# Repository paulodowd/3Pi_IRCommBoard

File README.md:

# 3Pi_IRCommBoard (work in progress)

## Features

- Can be considered a general purpose I2C extension board to provide local infra-red (IR) communication.
- IR Serial transmission at 4800 Baud.
- Transmit/receive upto 28 bytes (currently, extensible).
- Range can be reduced/set with a trimmer potentiometer.
- Effective IR transmit range approximately 30cm.
- Message corruption detection implemented with a CRC checksum.
- Designed to conveniently fit to an expansion header of the Pololu 3Pi+ mobile robot. 

## Summary

A pcb design to create infra-red (IR) communication between Pololu 3Pi+ robots. The design utilises an Arduino Pro Mini as an I2C Slave device.  The pro mini handles all transmit and receive operations over IR. The Master device (inteded as the 3Pi+, but could be any device with I2C) can upload a string to transmit, and also request the latest string received, if any.  This can get a little confusing to discuss: I2C is used to transfer messages between Master and Slave, and Serial/IR is used to tranmit messages between Slave devices.  

IR communication is implemented using the standard Serial functionality common to Arduino (e.g. `Serial.print()`), and so the IR circuit is electronically connected to  the Arduino TX and RX pins.  The detection (receiving) circuit uses a Demodulator chip that is tuned for a carrier frequency of 38.4Khz (more details below).  Therefore, the pro mini generates a 38Khz signal via an internal timer interrupt to provide the transmitting carrier, output on digital pin 4.  

The 38Khz carrier signal is combined electronically with the TX pin state through an OR gate (74xx32). The logic (OR) of this operation is defined by the gates sinking the current through the tranmitting IR LEDs.  Therefore, the LEDs are not driven by the 74xx32 (or the pro mini, to be clear), and are considered active low.  A nice unintended side effect of this is that when TX is inactive (LOW, not transmitting), the 74xx32 output is HIGH despite the continued 38Khz signal generation - which means the IR LEDs are off and not saturating the environment.

In this circuit design, a single gate is used to sink current.  It might be important to note that the <a href="https://www.ti.com/lit/ds/symlink/sn54hc32-sp.pdf">datasheet</a> for the logic gates specifies a max current sink of 50ma through ground - and here we are potentially sinking upto 250ma from the 5 IR LEDs.    So far, I've not seen any significant changes to performance and this may be because I am not sinking current continuously, instead intermitently at 38Khz. In a subsequent design (available <a href="https://github.com/paulodowd/Swarm-Bs">here</a>), all 4 gates are ganged, but the internal ground connection may still be a limitation. In either case, I haven't yet seen any problems or difference in performance.  It might be unwise to active the IR LEDs continuously.

Some messages transmitted over IR do get garbled.  As a quick solution, the firmware uses a CRC checksum.  I've used the same implementation as detailed on the RepRap wiki for GCode (<a href="https://reprap.org/wiki/G-code#Checking">here</a>).  Prior to transmitting, the pro mini generates a single byte checksum value, and appends this to the message string.  Therefore, when a message is received, the receiving pro mini completes the same CRC check on the received message for itself, and then compares if the checksum values match.  If not, some data must be corrupt and the message is discarded.  

The message strings transmitted between the pro mini devices would look something like:

`*message string@f`

Here, the `*` is used to identify the start of a message, the `@` is used to identify the end of the message and that the next byte is the checksum value.  In the example above, I haven't used the correct checksum value, it is just an illustrative example.  The transmission is also made with a `\n` character at the end, but this is discarded.  

At the moment, the pro mini firmware will only store 1 message, the latest message received.  Furthermore, it is programmed to erase this message after 1 second.  This suits the intended use of the board, but will likely need updating for other uses.  

When the Master device requests the latest message from the pro mini Slave device, it will receive a string terminated with a `!` character.  If the Master receives:

`!` 

This means that no messages are available.  Otherwise, the Master can parse the received bytes over I2C and use the `!` to identify the end of the string (more details below).  

If the Master is to set a string for the pro mini Slave to transmit over IR, this should be sent over I2C with no terminating character (e.g., no newline, or anything specific, just the string you wish to transmit).  Here, it is unknown (not tested!) what will happen if your string has an `*`, `\n` or `!` in it - it will probably break functionality!  Whilst this is inconsistent from the format used for messages between the pro mini Slave devices, it presents the simplest usage/interface when working with the Master device - all the tokens and CRC are handled for the user.

Software is still sketchy early work for proof-of-concept.

## Important Considerations

- **IR Demodulator:** I tried a few IR demodulator chips and they are not all created equally.  In particular, those designed to receive bursts of transmission appear poorly suited.  When using ones for burst transmission, I observed that I had to wave the transmitter or receiver around to get a successful transmission (perhaps some inner circuitry reaches a saturation?).  Instead it is better to use those designed for continuous transmission. The Vishay **TSDP34138** (<a href="https://www.farnell.com/datasheets/2245004.pdf">datasheet</a>) seems to fit this and works well / reliably.  The datasheet specifies upto 4800 baud for a 38.4Khz carrier frequency.  If you want to reproduce this board, I recommend you use the same device, or be ready for some trials of different devices.
- **IR Demodulator Placement:** The IR Demodulator (IRD) is placed central on the PCB and facing upwards - this probably isn't the manufacturers recommendation for optimal performance.  I did consider placing 5 IRD's around the circumference of the PCB facing outward between the IR LEDs.  However, the IRD is one of the more expensive components, and so producing 100 of these PCBs would be significantly more expensive with 5 IRD per board.  I have tested this PCB with 1 upward IRD and it can reliably detect IR transmission from neighbours at roughly 30cm distance.  For communication between Pololu 3Pi+ robots, this is relatively "local" and sufficient.  However, it does mean a robot cannot identify from which direction a transmission was received.  In theory, I think a more advanced version of this board could supply VCC to 5 independent IRD via the arduino digital pins, and therefore poll the IRD around the circumference of the board by enabling each in turn, and so infer directionality.  But I haven't tried this. 
- **Self-Receiving:** I did have an issue of a single board receiving it's own IR transmissions, and not being able to receive transmission from neighbours.  I believe this is because the UART implementation (on the Atmega328 at least) operates send (TX) and receive (RX) independently.  When using IR light, this means it will detect it's own transmission. After attempting a lot of different solutions, it was as simple as disabling the RX functionality of the UART by a register operation.  I'm glad this was available!  You can review the details of this on page 171 of the Atmega328 datasheet (<a href="https://ww1.microchip.com/downloads/en/DeviceDoc/Atmel-7810-Automotive-Microcontrollers-ATmega328P_Datasheet.pdf">here</a>).  You can find this operation in the firmware about <a href="https://github.com/paulodowd/3Pi_IRCommBoard/blob/922e04242b78fc39a44c0d518355c1a5028df249/arduino/pro_mini_firmware/pro_mini_firmware.ino#L243">here</a>.
- **Programming the Pro Mini:** It is important to note that the programming of the Pro Mini will most often fail if the IR Demodulator is electronically connected.  Therefore, the circuit design has a jumper (labelled, "RX Break") intended for a connecting removable sleeve, to allow the connection to be broken for programming.  Importantly, no IR messages can be received if this jumper is not closed with the sleeve.  
- **I2C requests from Master:** so far, it seems that the Master device has to request a specific number of bytes from the Slave device.  Because we don't necessarily know this before hand (and to take a short cut), the firmware has been written to append a `!` character to the end of the message string.  Therefore, the Master requests the maximum data length, and then parses for the `!` character.  After this, the data is gibberish.  In the future, it might be better to have a two step operation where the Master first asks how large the data to transfer is.  
- **Buffer Sizes:** The current buffers for sending and receiving IR messages in the firmware are set to 32 bytes (`MAX_MSG = 32`).  The IR transmission is operated by the Arduino Serial functionality.  By default, the Arduino environment sets the Serial buffer to 64 bytes.  Here, I decided to keep the Serial buffer under-utilised (half-full).  My un-tested rationale was to stand a chance of successfully parsing a whole 32-byte message within a 64-byte buffer.  I believe it is possible to expand the default Serial buffer beyond 64 bytes.  These aspects are open for investigation.  But for now, it is recommended to send a string of max length 28 bytes (leaving 4 bytes free for `*`, `@` and the checksum value).  The current buffer implementation for the IR messages is not very clever, e.g. not circular or anything like that.  I haven't validated the reliability of the transmission when the maximum buffer is used. 
- **Buffer Sizes:** The current buffers for sending and receiving IR messages in the firmware are set to 32 bytes (`MAX_MSG = 32`).  The IR transmission is operated by the Arduino Serial functionality.  By default, the Arduino environment sets the Serial buffer to 64 bytes.  Here, I decided to keep the Serial buffer under-utilised (half-full).  My un-tested rationale was to stand a chance of successfully parsing a whole 32-byte message within a 64-byte buffer.  I believe it is possible to expand the default Serial buffer beyond 64 bytes.  These aspects are open for investigation.  But for now, it is recommended to send a string of max length 28 bytes (leaving 3 bytes free for `*`, `@`, the checksum value and `\n`).  The current buffer implementation for the IR messages is not very clever, e.g. not circular or anything like that.  I haven't validated the reliability of the transmission when the maximum buffer is used. 
- **IR Message Buffers:** to buffer messages being sent and received, there are 3 buffers in total. 1) a buffer to hold the message to transmit as set by the Master 2) a buffer to process a received message 3) a buffer to hold the last correctly validated message to relay to the Master.  Therefore, buffer 2 could be considered volatile - hence the need for 3 buffers.  
- **IR LED current:**  In this circuit design, a single gate is used to sink current.  It might be important to note that the <a href="https://www.ti.com/lit/ds/symlink/sn54hc32-sp.pdf">datasheet</a> for the logic gates specifies a max current sink of 50ma through ground - and here we are potentially sinking upto 250ma from 5 IR LEDs.    So far, I've not seen any significant changes to performance and this may be because I am not sinking current continuously. In a subsequent design (available <a href="https://github.com/paulodowd/Swarm-Bs">here</a>), all 4 gates are ganged, but the internal ground connection may still be a limitation. In either case, I haven't yet seen any problems or difference in performance.  It might be unwise to active the IR LEDs continuously.

## Bill of Materials (BOM)

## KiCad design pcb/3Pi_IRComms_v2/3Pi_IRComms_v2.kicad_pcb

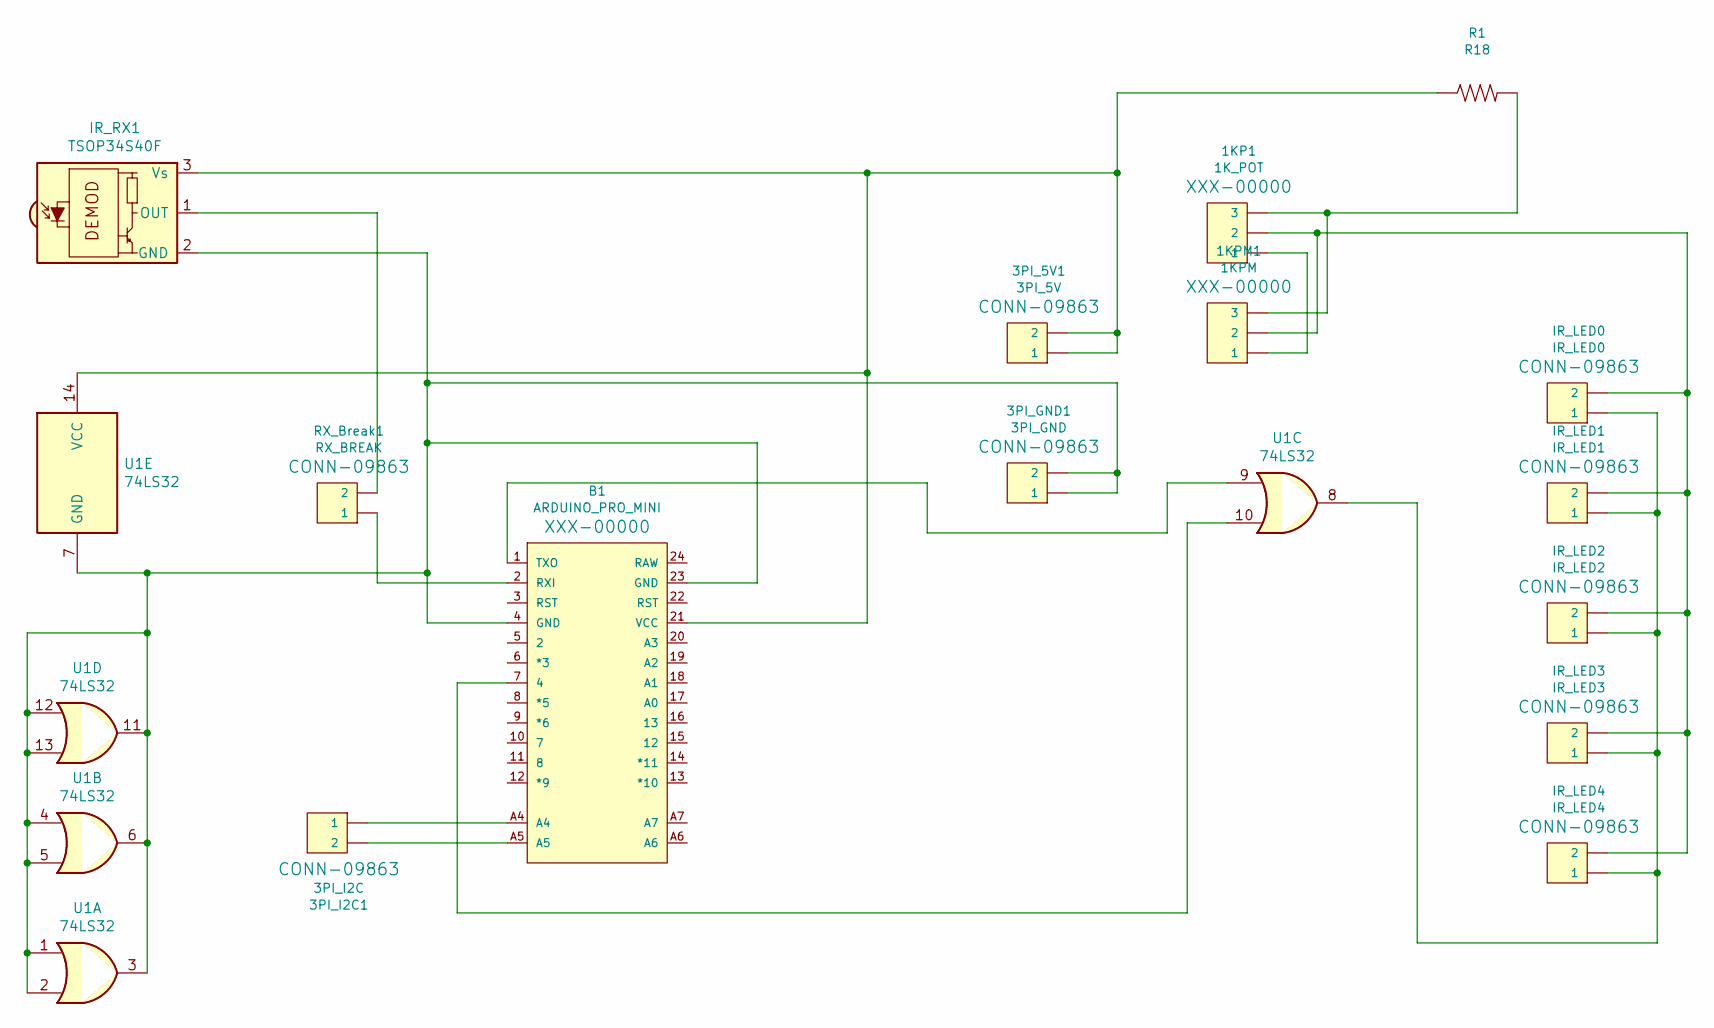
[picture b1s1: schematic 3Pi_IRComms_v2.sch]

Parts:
1KP1: 1K_POT; PinHeader_1x03_P2.54mm_Vertical
1KPM1: 1KPM; PinHeader_1x03_P2.54mm_Vertical
3PI_5V1: 3PI_5V; PinHeader_1x02_P2.54mm_Vertical
3PI_GND1: 3PI_GND; PinHeader_1x02_P2.54mm_Vertical
3PI_I2C1: 3PI_I2C; PinHeader_1x02_P2.54mm_Vertical
B1: ARDUINO_PRO_MINI
IR_LED0: IR_LED0; PinHeader_1x02_P2.54mm_Vertical
IR_LED1: IR_LED1; PinHeader_1x02_P2.54mm_Vertical
IR_LED2: IR_LED2; PinHeader_1x02_P2.54mm_Vertical
IR_LED3: IR_LED3; PinHeader_1x02_P2.54mm_Vertical
IR_LED4: IR_LED4; PinHeader_1x02_P2.54mm_Vertical
IR_RX1: TSOP34S40F; Vishay_MOLD-3Pin
R1: R18; PinHeader_1x02_P2.54mm_Vertical
RX_Break1: RX_BREAK; PinHeader_1x02_P2.54mm_Vertical
U1: 74LS32; DIP-14_W7.62mm_Socket

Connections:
unnamed: 1KP1.1, 1KPM1.1
unnamed: 1KP1.2, 1KPM1.2, IR_LED0.2, IR_LED1.2, IR_LED2.2, IR_LED3.2, IR_LED4.2
unnamed: 1KP1.3, 1KPM1.3, R1.2
unnamed: 3PI_5V1.1, 3PI_5V1.2, B1.21 (VCC), IR_RX1.3 (Vs), R1.1, U1.14 (VCC)
unnamed: 3PI_GND1.1, 3PI_GND1.2, B1.4 (GND), B1.23 (GND), IR_RX1.2 (GND), U1.1, U1.2, U1.3, U1.4, U1.5, U1.6, U1.7 (GND), U1.11, U1.12, U1.13
unnamed: 3PI_I2C1.1, B1.A4
unnamed: 3PI_I2C1.2, B1.A5
unnamed: B1.1 (TXO), U1.9
unnamed: B1.2 (RXI), RX_Break1.1
unnamed: B1.7 (4), U1.10
unnamed: IR_LED0.1, IR_LED1.1, IR_LED2.1, IR_LED3.1, IR_LED4.1, U1.8
unnamed: IR_RX1.1 (OUT), RX_Break1.2

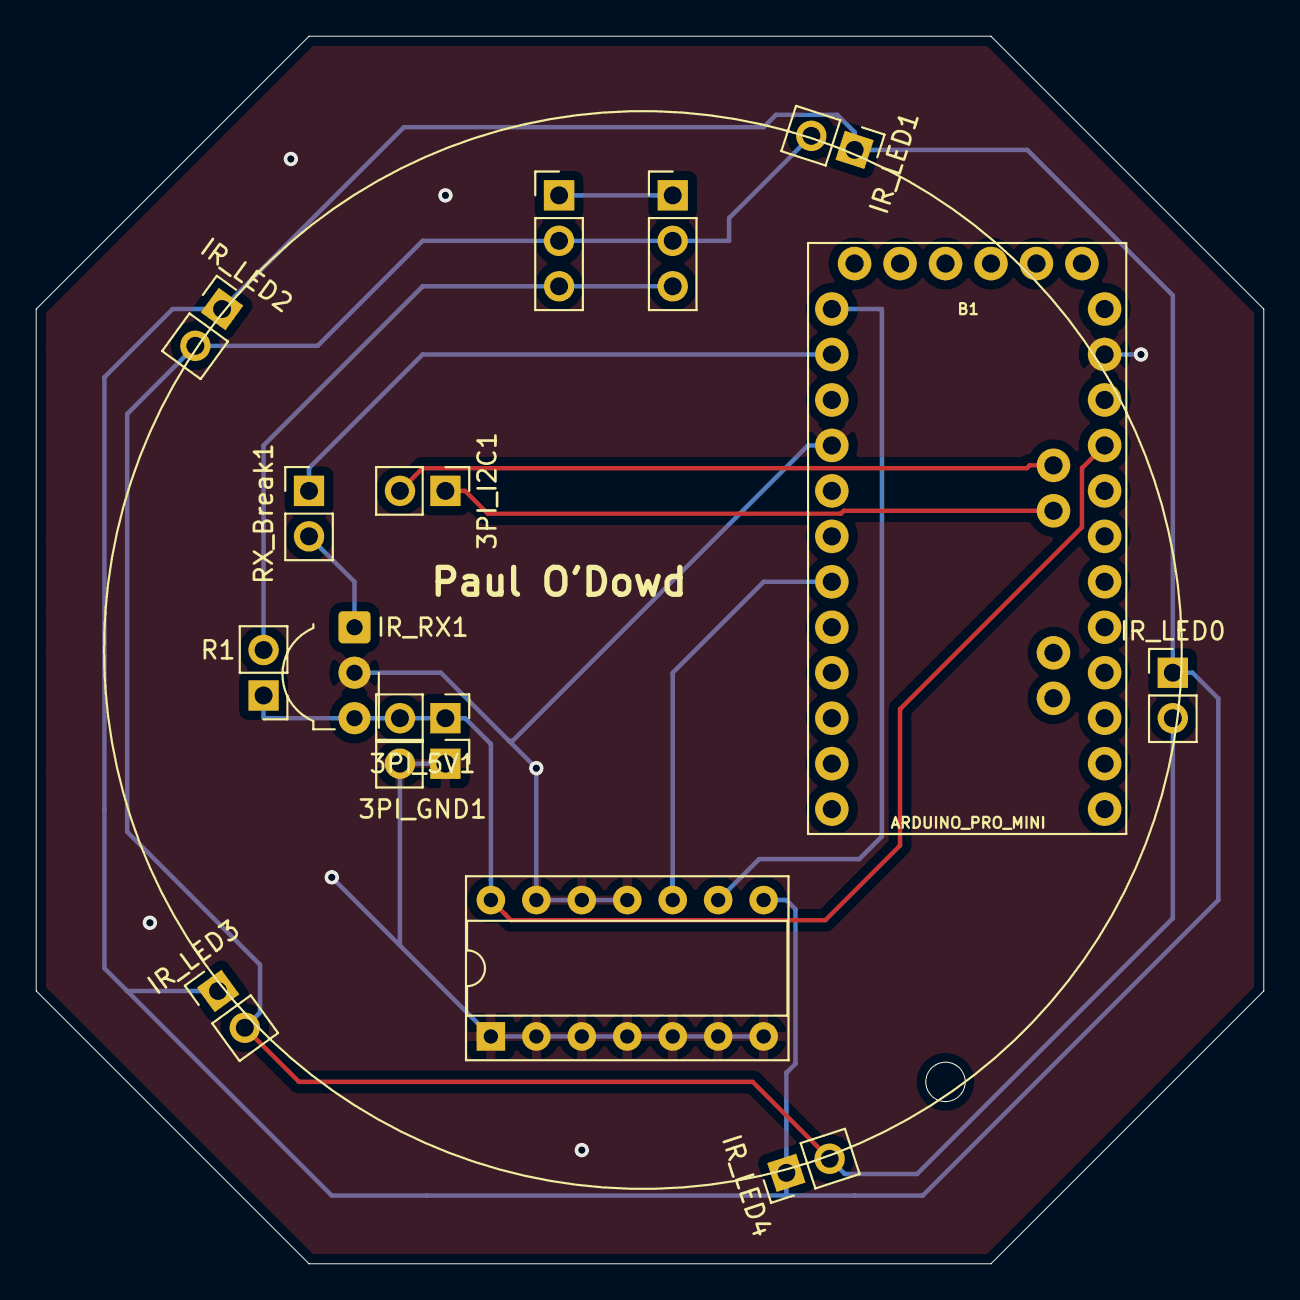
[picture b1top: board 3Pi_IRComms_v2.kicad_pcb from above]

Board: 2 copper layers, 68.6 x 68.6 mm, 15 parts (0 on the bottom side), 12 nets.

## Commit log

2022-03-15 setup
2022-03-16 fixed buffer error rx_count in firmware
2022-03-16 updated gerber files
2022-03-17 minor update to readme
2022-07-27 update to firmware versions
2022-07-27 update to firmware
2022-10-04 Created using Colaboratory
